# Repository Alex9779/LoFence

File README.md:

# LoFence V2

LoFence V2 is an updated version of the original [LoFence](https://github.com/kiu/lofence/) tackling a few shortcomings.

The main improvements are:

- case lid can be opened while main body is mounted,
- two batteries for a longer operating time,
- battery deep discharge protection using an activation circuit with a button triggered from the firmware when batteries run low,
- fully revised firmware with ability to change operating parameters by downlinks.

Other things changed are:

- Exchange RN2483 module for Dragino LA66.
  - I always had some problems with the RN2483 though serial communication protocol was easier to work with.
  - LA66 has antenna connector on board so I don't have to care about a correct antenna circuit which also has to follow the guidelines to not to violate regulatory approvals.
  - LA66 is a little cheaper.
- Implement probe resistor divider erratum.
- Optimized for assembling.
  - Changed various components to SMD variants.
  - Switch to buck-boost converter for power supply.
  - Use clamps for holding batteries instead of full holder.

For information how to build a LoFence V2 device see the [hardware repository](https://github.com/Alex9779/LoFence_Hardware).

For information how to build, upload or configure the firmware see the [firmware repository](https://github.com/Alex9779/LoFence_Firmware).

## WARNING

Do not let the debug LEDs activated during normal operation!

They need a lot of current compared to the overall device's current usage. So if activated they drastically reduce the battery runtime to just some weeks or even days.

## Device activation

The LoFence V2 is equipped with an activation circuit allowing the device to deactivate itself if the battery voltage goes under a configured level (3200mV by default for 5 cycles or 3100mV as an absolute minumum) to prevent the battery from deep discharge.

Therefore the device does not automatically activate if a battery is put in but you have to push and hold the *ACTIVATE* button for at least 1 second.

If the debug LEDs are activated the *IDLE* LED indicates that the activation process has been completed when it goes out.

After activation the device tries to join (re-join) the network, LoRaWAN counters are reset.

If joining succeeds the device will immediately do the first measurement and after that transmits the first uplink.

## Device resetting

To reset the device push the *RESET* button. After a reset the device has to be activated again.

A reset is just the same as removing all batteries and put them back in and activate the device.

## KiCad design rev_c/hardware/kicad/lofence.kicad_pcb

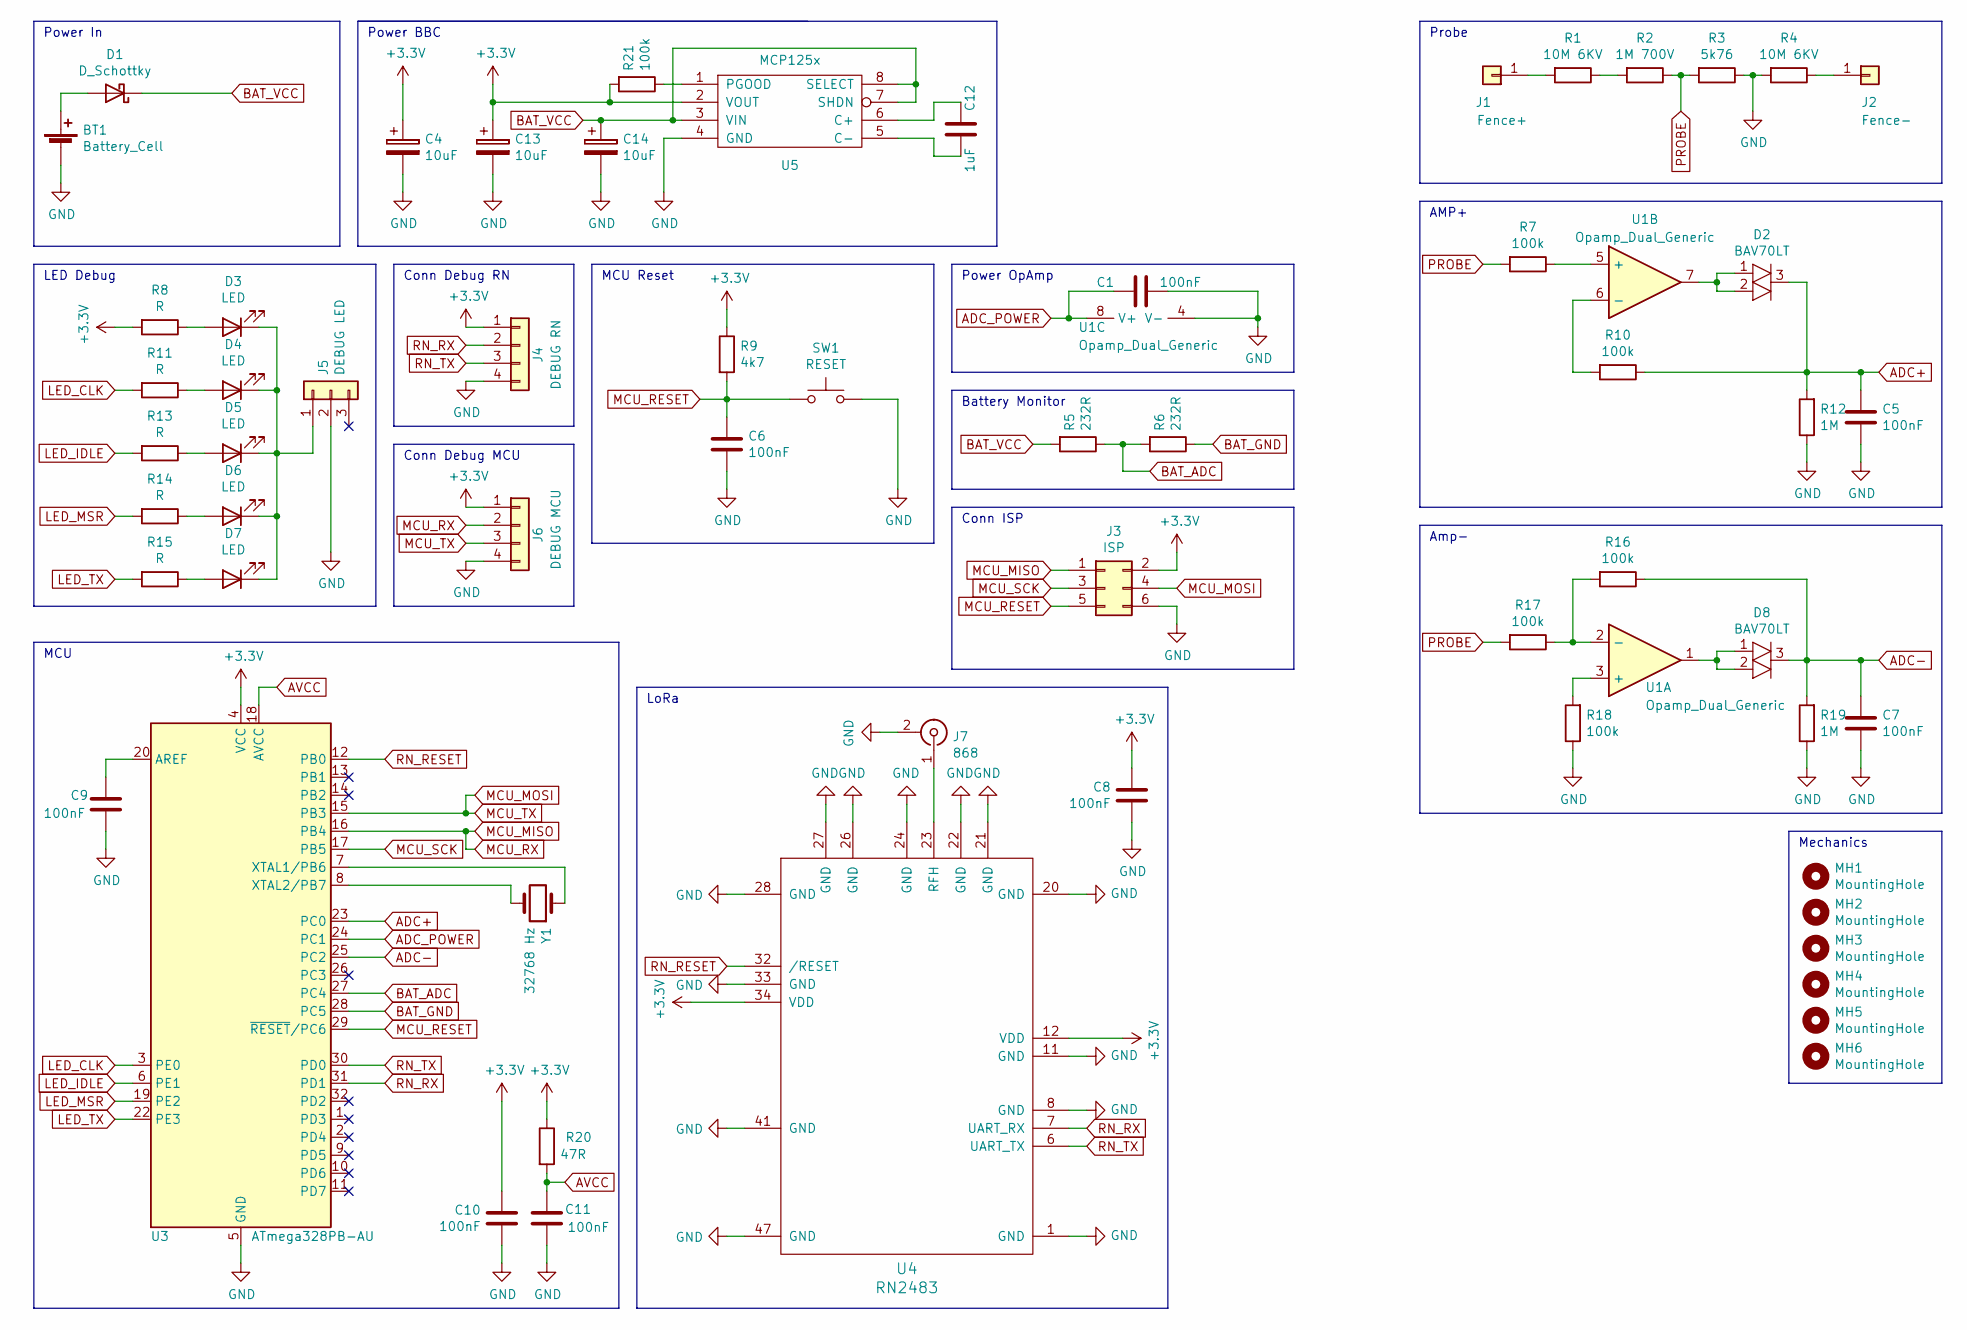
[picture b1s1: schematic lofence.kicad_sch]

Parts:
BT1: Battery_Cell; 18650HolderTHT
C1, C5, C6, C7, C8, C9, C10, C11: 100nF; C_0805_2012Metric_Pad1.18x1.45mm_HandSolder
C4: 10uF; CP_Elec_4x5.7
C12: 1uF; C_0805_2012Metric_Pad1.18x1.45mm_HandSolder
C13, C14: 10uF; C_1206_3216Metric_Pad1.33x1.80mm_HandSolder
D1: D_Schottky; D_SMA_Handsoldering
D2, D8: BAV70LT; SOT-23
D3, D4, D5, D6, D7: LED; LED_0805_2012Metric_Pad1.15x1.40mm_HandSolder
J1: Fence+; TestPoint_THTPad_4.0x4.0mm_Drill2.0mm
J2: Fence-; TestPoint_THTPad_4.0x4.0mm_Drill2.0mm
J3: ISP; PinHeader_2x03_P2.54mm_Vertical
J4: DEBUG RN; PinHeader_1x04_P2.54mm_Vertical
J5: DEBUG LED; PinHeader_1x03_P2.54mm_Vertical
J6: DEBUG MCU; PinHeader_1x04_P2.54mm_Vertical
J7: 868; U.FL
MH1, MH2, MH3, MH4, MH5, MH6: MountingHole; MountingHole_2.7mm_M2.5
R1, R4: 10M 6KV; R_Axial_DIN0516_L15.5mm_D5.0mm_P20.32mm_Horizontal
R2: 1M 700V; R_Axial_DIN0207_L6.3mm_D2.5mm_P10.16mm_Horizontal
R3: 5k76; R_0805_2012Metric_Pad1.20x1.40mm_HandSolder
R5, R6: 232R; R_0805_2012Metric_Pad1.20x1.40mm_HandSolder
R7, R10, R16, R17, R18, R21: 100k; R_0805_2012Metric_Pad1.20x1.40mm_HandSolder
R8, R11, R13, R14, R15: R; R_0805_2012Metric_Pad1.20x1.40mm_HandSolder
R9: 4k7; R_0805_2012Metric_Pad1.20x1.40mm_HandSolder
R12, R19: 1M; R_0805_2012Metric_Pad1.20x1.40mm_HandSolder
R20: 47R; R_0805_2012Metric_Pad1.20x1.40mm_HandSolder
SW1: RESET; SW_SPST_B3SL-1002P
U1: Opamp_Dual_Generic; SOIC-8_3.9x4.9mm_P1.27mm
U3: ATmega328PB-AU; TQFP-32_7x7mm_P0.8mm
U4: RN2483; RN2483_serial
U5: MCP125x; MSOP-8_3x3mm_P0.65mm
Y1: 32768 Hz; Crystal_Round_D3.0mm_Vertical

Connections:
+3V3: C4.1, C8.2, C10.2, C13.1, J3.2, J4.1, J6.1, R8.2, R9.1, R20.1, R21.2, U3.4 (VCC), U4.12 (VDD), U4.34 (VDD), U5.2 (VOUT)
ADC+: C5.1, D2.3 (K), R10.1, R12.2, U3.23 (PC0)
ADC-: C7.1, D8.3 (K), R16.1, R19.2, U3.25 (PC2)
ADC_POWER: C1.1, U1.8 (V+), U3.24 (PC1)
AVCC: C11.2, R20.2, U3.18 (AVCC)
BAT_ADC: R5.1, R6.2, U3.27 (PC4)
BAT_GND: R6.1, U3.28 (PC5)
BAT_VCC: C14.1, D1.1 (K), R5.2, U5.3 (VIN), U5.7 (SHDN), U5.8 (SELECT)
GND: BT1.2 (-), C1.2, C4.2, C5.2, C6.2, C7.2, C8.1, C9.2, C10.1, C11.1, C13.2, C14.2, J3.6, J4.4, J5.2, J6.4, J7.2 (Ext), R3.1, R4.2, R12.1, R18.1, R19.1, SW1.2, U1.4 (V-), U3.5 (GND), U3.21 (GND), U4.1 (GND), U4.8 (GND), U4.11 (GND), U4.20 (GND), U4.21 (GND), U4.22 (GND), U4.24 (GND), U4.26 (GND), U4.27 (GND), U4.28 (GND), U4.33 (GND), U4.41 (GND), U4.47 (GND), U5.4 (GND)
LED_CLK: R11.2, U3.3 (PE0)
LED_IDLE: R13.2, U3.6 (PE1)
LED_MSR: R14.2, U3.19 (PE2)
LED_TX: R15.2, U3.22 (PE3)
MCU_MISO: J3.1, J6.2, U3.16 (PB4)
MCU_MOSI: J3.4, J6.3, U3.15 (PB3)
MCU_RESET: C6.1, J3.5, R9.2, SW1.1, U3.29 (~RESET/PC6)
MCU_SCK: J3.3, U3.17 (PB5)
unnamed: BT1.1 (+), D1.2 (A)
unnamed: C9.1, U3.20 (AREF)
unnamed: C12.1, U5.6 (C+)
unnamed: C12.2, U5.5 (C-)
unnamed: D2.1 (A1), D2.2 (A2), U1.7
unnamed: D3.1 (K), D4.1 (K), D5.1 (K), D6.1 (K), D7.1 (K), J5.1
unnamed: D3.2 (A), R8.1
unnamed: D4.2 (A), R11.1
unnamed: D5.2 (A), R13.1
unnamed: D6.2 (A), R14.1
unnamed: D7.2 (A), R15.1
unnamed: D8.1 (A1), D8.2 (A2), U1.1
unnamed: J1.1, R1.2
unnamed: J2.1, R4.1
unnamed: J7.1 (In), U4.23 (RFH)
unnamed: R1.1, R2.2
unnamed: R7.1, U1.5 (+)
unnamed: R10.2, U1.6 (-)
unnamed: R16.2, R17.1, U1.2 (-)
unnamed: R18.2, U1.3 (+)
unnamed: R21.1, U5.1 (PGOOD)
unnamed: U3.7 (XTAL1/PB6), Y1.1
unnamed: U3.8 (XTAL2/PB7), Y1.2
PROBE: R2.1, R3.2, R7.2, R17.2
RN_RESET: U3.12 (PB0), U4.32 (/RESET)
RN_RX: J4.2, U3.31 (PD1), U4.7 (UART_RX)
RN_TX: J4.3, U3.30 (PD0), U4.6 (UART_TX)

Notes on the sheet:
Power BBC
Conn ISP
Battery Monitor
Conn Debug MCU
AMP+
MCU
Conn Debug RN
Mechanics
Power In
MCU Reset
Power OpAmp
LoRa
LED Debug
Probe
Amp-

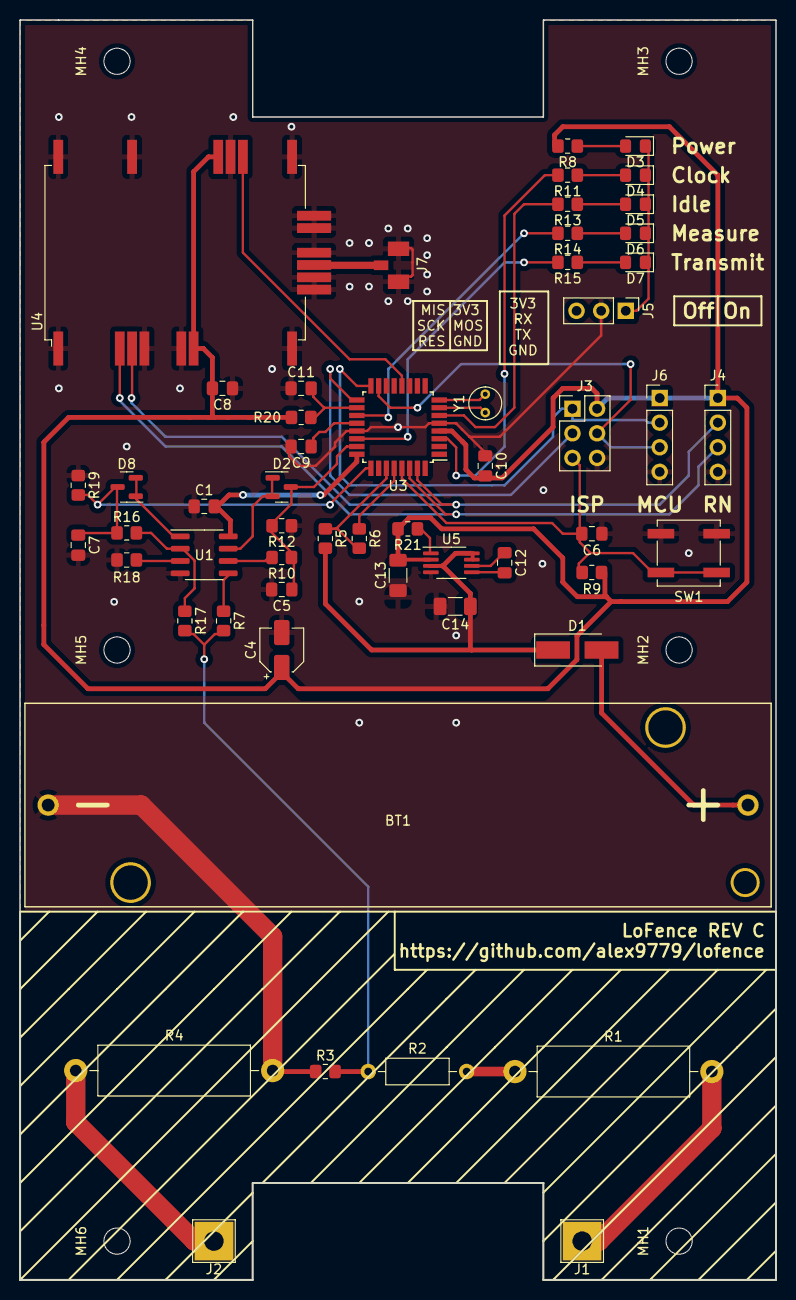
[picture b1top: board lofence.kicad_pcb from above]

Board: 2 copper layers, 78.0 x 130.0 mm, 61 parts (0 on the bottom side), 44 nets.

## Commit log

2023-08-15 rev_c firmware
2023-08-15 clean spaces
2023-08-15 remove saving of uplink counter
2023-08-15 remove upctr, use lora fCnt instead
2023-08-15 update ignores
2023-08-15 create rev c
    - adapt errata of rev b
    - update symbols and footprints
    - clean board
2023-08-15 additional cleaning
2023-08-15 fix battery power
2023-10-14 initial commit for V2
2023-10-14 add firmware and hardware repo as module
2023-10-14 add decoder scripts
2023-10-18 implement decoding settings
2023-10-19 add calculations
2023-10-19 update decoders
2023-11-24 HW rev1.0, FW v1.0
2023-11-25 adjust decoder for v1.0 firmware
2023-11-25 change object creation
2023-11-25 add decoder with location from variables
2023-11-26 fix decoders
2023-11-26 add decoding of error uplink
2023-11-27 firmware v1.1
2024-02-02 firmware to v1.2 and decoders for it
2024-03-03 update firmware submodule to v1.2-1
2024-04-15 update firmware submodule to v1.2-3
2024-04-15 Fix TTN decoder for FW1.2
